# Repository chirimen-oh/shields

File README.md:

# CHIRIMEN Shields collection
## Description

### CHIRIMENBlankShield (eagle file)

CHIRIMENBlankShield has only the same pins and drill holes as CHIRIMEN CMN2015-1 board has.

### CHIRIMENBasicShield (eagle file)

CHIRIMENBasicShield allows you to try CHIRIMEN basic examples. It has a LED, a button, pin holes for ADT7410 and SRF02, and ten grove connectors.

### CHRMN-PROT-SHIELD

The CHRMN-PROT-SHIELD fits on to your CHIRIMEN board, it makes easy for you to design custom circuits.

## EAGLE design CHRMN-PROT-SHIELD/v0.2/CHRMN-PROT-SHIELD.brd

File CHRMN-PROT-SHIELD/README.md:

---
shield name: CHRMN-PROT-SHIELD
designer: D.F.Mac. (H.Kodama)
version: 0.2
date:2016.10.13
status: OK
---

## desc

`CHRMN-PROT-SHIELD`は2.54mmピッチのユニバーサル基板シールドです。

## design

Eagle 7.3で作成しています。詳細は下記を参照ください。

- [board(v0.2)](./v0.1/CHRMN-PROT-SHIELD.brd)
- [Schematic(v0.2)](./v0.1/CHRMN-PROT-SHIELD.sch)

### garber files

[Elecrow](https://www.elecrow.com/)用に出力したgarberファイルです。
2upデータにしてあります。10cm×10cmサイズで発注可能です。

- [v0.2](./v0.2/forELECROW)

## License

[CHIRIME License](https://chirimen.org/license/)を参照ください。

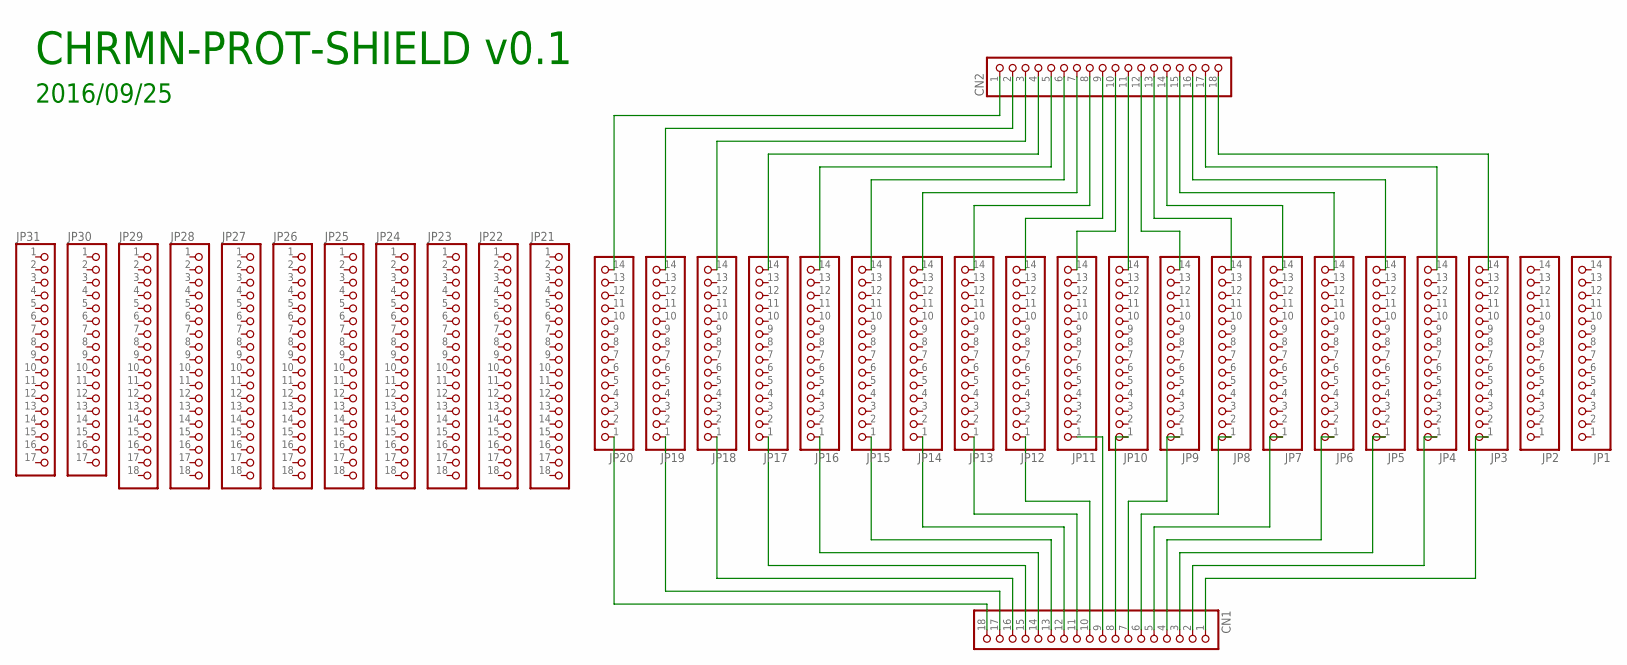
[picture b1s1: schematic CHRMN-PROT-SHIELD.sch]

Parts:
CN1, CN2: PINHD-1X18; 1X18
JP1, JP2, JP3, JP4, JP5, JP6, JP7, JP8, JP9, JP10, JP11, JP12, JP13, JP14, JP15, JP16, JP17, JP18, JP19, JP20: PINHD-1X141X14-N; N-PHEAD-1_14
JP21, JP22, JP23, JP24, JP25, JP26, JP27, JP28, JP29: PINHD-1X181X18-N; N-PHEAD-1_18
JP30, JP31: PINHD-1X171X17N; N-PHEAD-1_17

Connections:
unnamed: CN2.18, JP3.14
unnamed: CN2.17, JP4.14
unnamed: CN2.16, JP5.14
unnamed: CN2.15, JP6.14
unnamed: CN2.14, JP7.14
unnamed: CN2.13, JP8.14
unnamed: CN2.12, JP9.14
unnamed: CN2.11, JP10.14
unnamed: CN2.10, JP11.14
unnamed: CN2.9, JP12.14
unnamed: CN2.8, JP13.14
unnamed: CN2.7, JP14.14
unnamed: CN2.6, JP15.14
unnamed: CN2.5, JP16.14
unnamed: CN2.4, JP17.14
unnamed: CN2.3, JP18.14
unnamed: CN2.2, JP19.14
unnamed: CN2.1, JP20.14
unnamed: CN1.1, JP3.1
unnamed: CN1.2, JP4.1
unnamed: CN1.3, JP5.1
unnamed: CN1.4, JP6.1
unnamed: CN1.5, JP7.1
unnamed: CN1.6, JP8.1
unnamed: CN1.7, JP9.1
unnamed: CN1.8, JP10.1
unnamed: CN1.9, JP11.1
unnamed: CN1.10, JP12.1
unnamed: CN1.11, JP13.1
unnamed: CN1.12, JP14.1
unnamed: CN1.13, JP15.1
unnamed: CN1.14, JP16.1
unnamed: CN1.15, JP17.1
unnamed: CN1.16, JP18.1
unnamed: CN1.17, JP19.1
unnamed: CN1.18, JP20.1

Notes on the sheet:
CHRMN-PROT-SHIELD v0.1
2016/09/25

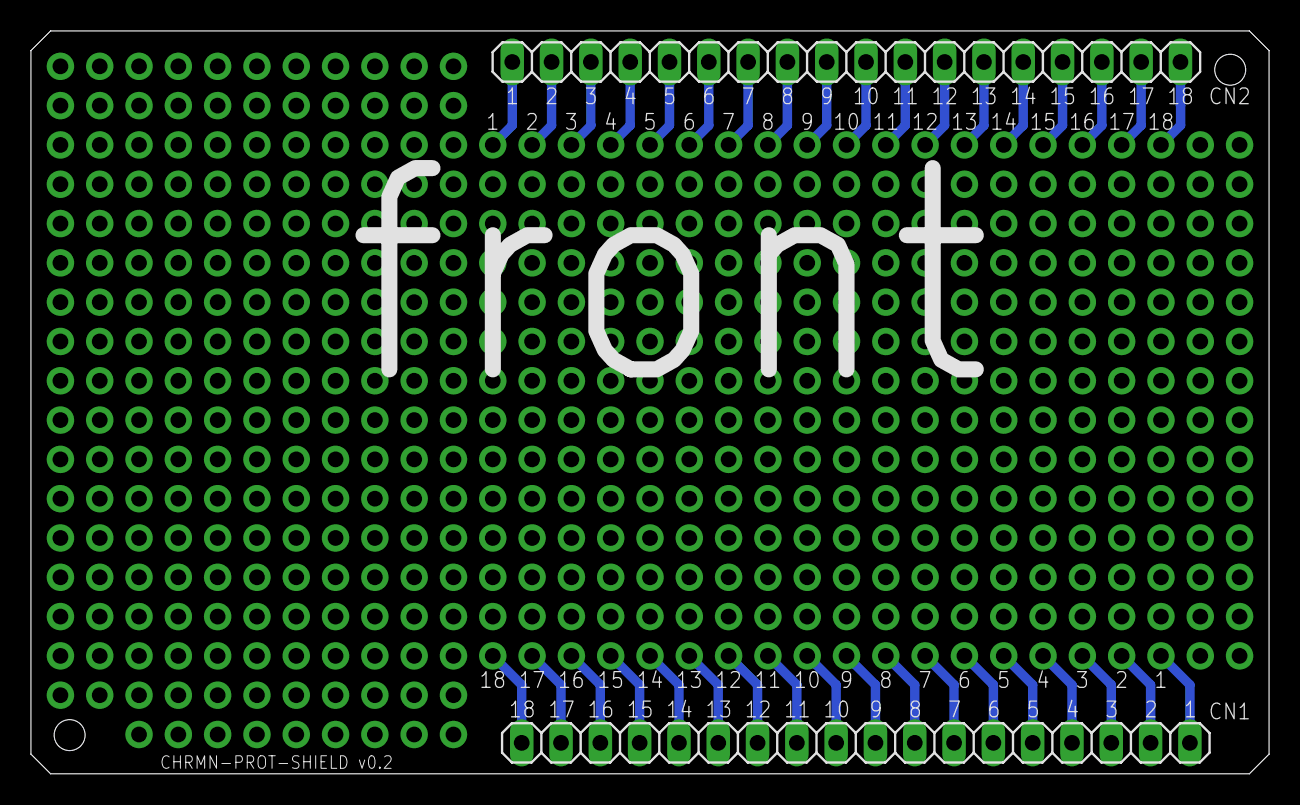
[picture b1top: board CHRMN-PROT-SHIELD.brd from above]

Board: 2 copper layers, 80.0 x 48.0 mm, 33 parts (0 on the bottom side), 36 nets.

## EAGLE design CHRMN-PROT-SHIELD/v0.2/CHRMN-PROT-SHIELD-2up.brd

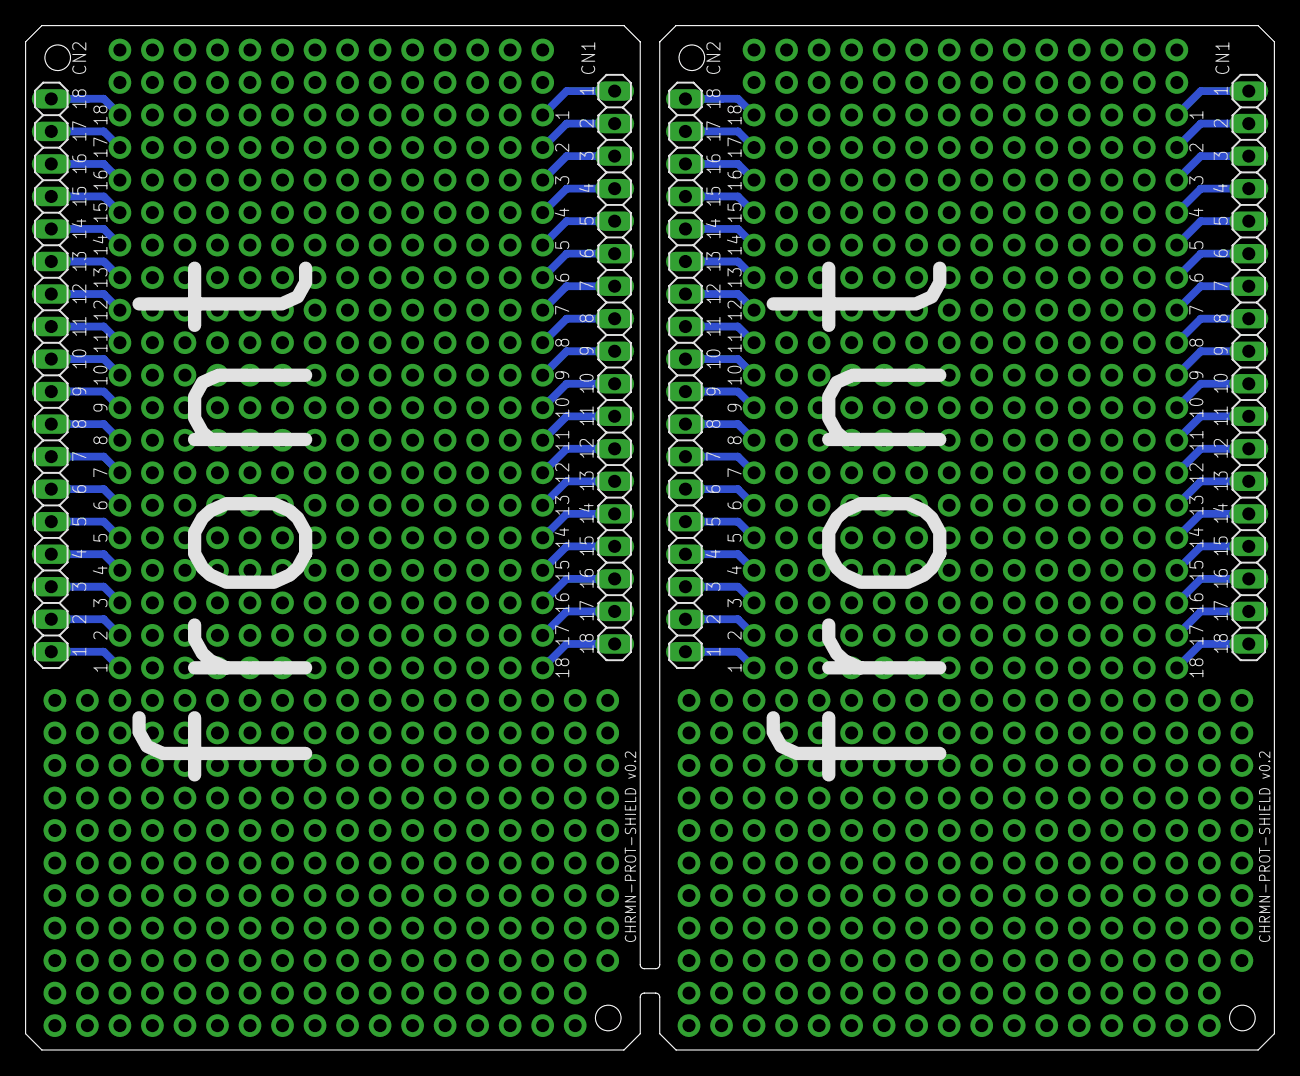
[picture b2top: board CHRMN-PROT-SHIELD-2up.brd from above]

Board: 2 copper layers, 97.5 x 80.0 mm, 66 parts (0 on the bottom side), 72 nets.

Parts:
CN1, CN2, CN3, CN4: 1X18
JP1, JP2, JP3, JP4, JP5, JP6, JP7, JP8, JP9, JP10, JP11, JP12, JP13, JP14, JP15, JP16, JP17, JP18, JP19, JP20, JP32, JP33, JP34, JP35, JP36, JP37, JP38, JP39, JP40, JP41, JP42, JP43, JP44, JP45, JP46, JP47, JP48, JP49, JP50, JP51: N-PHEAD-1_14
JP21, JP22, JP23, JP24, JP25, JP26, JP27, JP28, JP29, JP52, JP53, JP54, JP55, JP56, JP57, JP58, JP59, JP60: N-PHEAD-1_18
JP30, JP31, JP61, JP62: N-PHEAD-1_17

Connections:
unnamed: CN2.18, JP3.14
unnamed: CN2.17, JP4.14
unnamed: CN2.16, JP5.14
unnamed: CN2.15, JP6.14
unnamed: CN2.14, JP7.14
unnamed: CN2.13, JP8.14
unnamed: CN2.12, JP9.14
unnamed: CN2.11, JP10.14
unnamed: CN2.10, JP11.14
unnamed: CN2.9, JP12.14
unnamed: CN2.8, JP13.14
unnamed: CN2.7, JP14.14
unnamed: CN2.6, JP15.14
unnamed: CN2.5, JP16.14
unnamed: CN2.4, JP17.14
unnamed: CN2.3, JP18.14
unnamed: CN2.2, JP19.14
unnamed: CN2.1, JP20.14
unnamed: CN1.1, JP3.1
unnamed: CN1.2, JP4.1
unnamed: CN1.3, JP5.1
unnamed: CN1.4, JP6.1
unnamed: CN1.5, JP7.1
unnamed: CN1.6, JP8.1
unnamed: CN1.7, JP9.1
unnamed: CN1.8, JP10.1
unnamed: CN1.9, JP11.1
unnamed: CN1.10, JP12.1
unnamed: CN1.11, JP13.1
unnamed: CN1.12, JP14.1
unnamed: CN1.13, JP15.1
unnamed: CN1.14, JP16.1
unnamed: CN1.15, JP17.1
unnamed: CN1.16, JP18.1
unnamed: CN1.17, JP19.1
unnamed: CN1.18, JP20.1
unnamed: CN4.18, JP34.14
unnamed: CN4.17, JP35.14
unnamed: CN4.16, JP36.14
unnamed: CN4.15, JP37.14
unnamed: CN4.14, JP38.14
unnamed: CN4.13, JP39.14
unnamed: CN4.12, JP40.14
unnamed: CN4.11, JP41.14
unnamed: CN4.10, JP42.14
unnamed: CN4.9, JP43.14
unnamed: CN4.8, JP44.14
unnamed: CN4.7, JP45.14
unnamed: CN4.6, JP46.14
unnamed: CN4.5, JP47.14
unnamed: CN4.4, JP48.14
unnamed: CN4.3, JP49.14
unnamed: CN4.2, JP50.14
unnamed: CN4.1, JP51.14
unnamed: CN3.1, JP34.1
unnamed: CN3.2, JP35.1
unnamed: CN3.3, JP36.1
unnamed: CN3.4, JP37.1
unnamed: CN3.5, JP38.1
unnamed: CN3.6, JP39.1
unnamed: CN3.7, JP40.1
unnamed: CN3.8, JP41.1
unnamed: CN3.9, JP42.1
unnamed: CN3.10, JP43.1
unnamed: CN3.11, JP44.1
unnamed: CN3.12, JP45.1
unnamed: CN3.13, JP46.1
unnamed: CN3.14, JP47.1
unnamed: CN3.15, JP48.1
unnamed: CN3.16, JP49.1
unnamed: CN3.17, JP50.1
unnamed: CN3.18, JP51.1

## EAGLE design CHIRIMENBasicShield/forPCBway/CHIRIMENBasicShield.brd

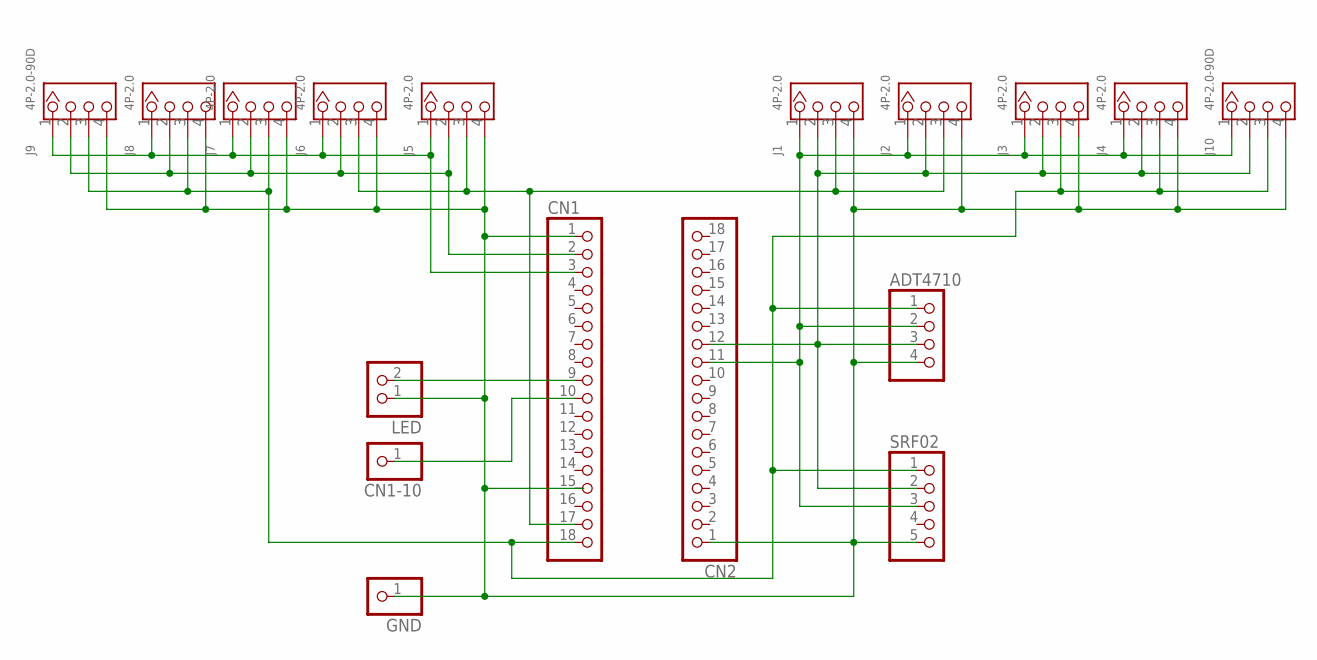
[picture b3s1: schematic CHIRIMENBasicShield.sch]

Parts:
ADT4710: PINHD-1X4; 1X04
CN1, CN2: PINHD-1X18; 1X18
CN1-10: PINHD-1X1; 1X01
GND: PINHD-1X1; 1X01
J1, J2, J3, J4, J5, J6, J7, J8: 4P-2.0; HW4-2.0
J9, J10: 4P-2.0-90D; HW4-2.0-90D
LED: PINHD-1X2; 1X02
SRF02: PINHD-1X5; 1X05

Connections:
3V3: CN1.17, J1.3, J2.3, J5.3, J6.3
5V: ADT4710.1, CN1.18, J3.3, J4.3, J7.3, J8.3, J9.3, J10.3, SRF02.1
GND: ADT4710.4, CN1.1, CN2.1, GND.1, J1.4, J2.4, J3.4, J4.4, J5.4, J6.4, J7.4, J8.4, J9.4, J10.4, LED.1, SRF02.5
unnamed: CN1.10, CN1-10.1
unnamed: CN1.2, J5.2, J6.2, J7.2, J8.2, J9.2
unnamed: CN1.3, J5.1, J6.1, J7.1, J8.1, J9.1
unnamed: ADT4710.3, CN2.12, J1.2, J2.2, J3.2, J4.2, J10.2, SRF02.2
unnamed: ADT4710.2, CN2.11, J1.1, J2.1, J3.1, J4.1, J10.1, SRF02.3
unnamed: CN1.9, LED.2

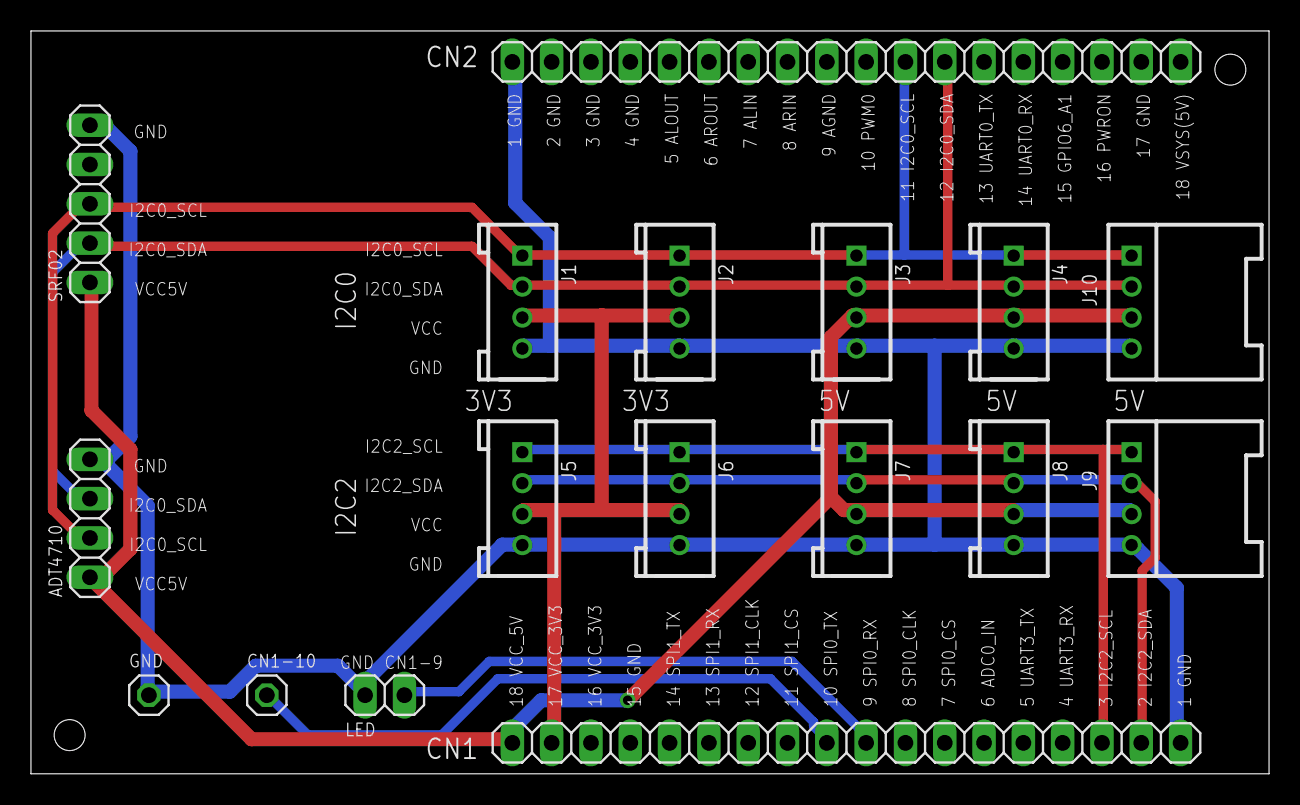
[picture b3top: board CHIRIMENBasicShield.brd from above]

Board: 2 copper layers, 80.0 x 48.0 mm, 17 parts (0 on the bottom side), 9 nets.

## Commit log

2016-06-08 first commit: add CHIRIMEN Basic Shield and Blank Shield
2016-07-11 issues #45,46
2016-09-25 add CHRMN-PROT-SHIELD files (1st commit)
2016-09-25 CHRMN-PROT-SHIELD: fix readme.md
2016-10-13 readme.md : add desc for CHRMN-PROT-SHIELD
2016-10-13 CHIRMN-PROT-SHIELD/readme.md update status
2016-10-13 CHRMN-PROT-SHIELD update to v0.2
2016-10-13 CHRMN-PROT-SHIELD: update garber files to 0.2
